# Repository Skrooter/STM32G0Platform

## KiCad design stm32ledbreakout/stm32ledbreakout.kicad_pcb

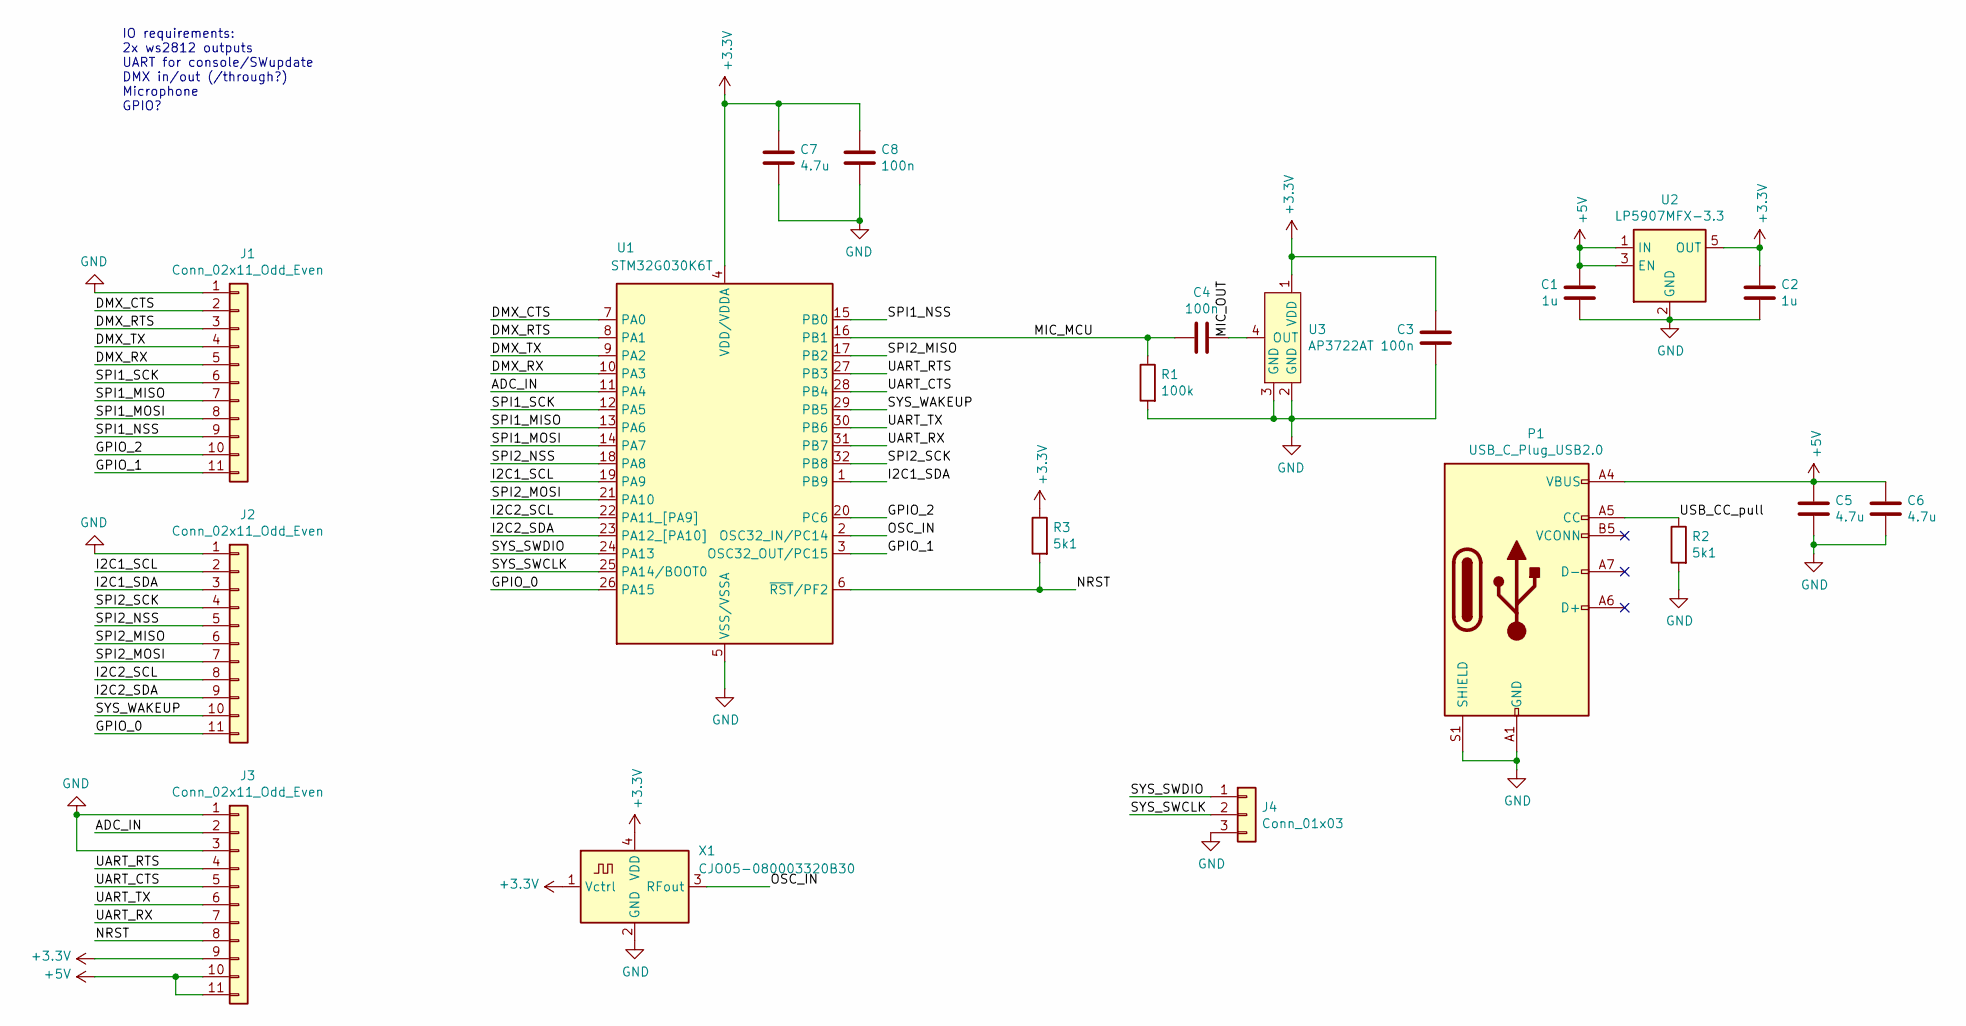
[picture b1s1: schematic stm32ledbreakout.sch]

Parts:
C1, C2: 1u; C_0603_1608Metric_Pad1.08x0.95mm_HandSolder
C3, C4, C8: 100n; C_0603_1608Metric_Pad1.08x0.95mm_HandSolder
C5, C6, C7: 4.7u; C_0603_1608Metric_Pad1.08x0.95mm_HandSolder
J1, J2, J3: Conn_02x11_Odd_Even; Castillation_11_P2.54mm
J4: Conn_01x03; PinSocket_1x03_P2.54mm_Vertical
P1: USB_C_Plug_USB2.0; USB_C_Receptacle_HRO_TYPE-C-31-M-12
R1: 100k; R_0603_1608Metric
R2, R3: 5k1; R_0603_1608Metric
U1: STM32G030K6T; LQFP-32_7x7mm_P0.8mm
U2: LP5907MFX-3.3; SOT-23-5
U3: AP3722AT
X1: CJO05-080003320B30; Oscillator_SMD_Abracon_ASE-4Pin_3.2x2.5mm_HandSoldering

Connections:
+3V3: C2.1, C3.1, C7.1, C8.2, J3.9, R3.1, U1.4 (VDD/VDDA), U2.5 (OUT), U3.1 (VDD), X1.1 (Vctrl), X1.4 (VDD)
+5V: C1.2, C5.1, C6.1, J3.10, J3.11, P1.A4 (VBUS), P1.A9 (VBUS), P1.B4 (VBUS), P1.B9 (VBUS), U2.1 (IN), U2.3 (EN)
/ADC_IN: J3.2, U1.11 (PA4)
/DMX_CTS: J1.2, U1.7 (PA0)
/DMX_RTS: J1.3, U1.8 (PA1)
/DMX_RX: J1.5, U1.10 (PA3)
/DMX_TX: J1.4, U1.9 (PA2)
/GPIO_0: J2.11, U1.26 (PA15)
/GPIO_1: J1.11, U1.3 (OSC32_OUT/PC15)
/GPIO_2: J1.10, U1.20 (PC6)
/I2C1_SCL: J2.2, U1.19 (PA9)
/I2C1_SDA: J2.3, U1.1 (PB9)
/I2C2_SCL: J2.8, U1.22 (PA11_[PA9])
/I2C2_SDA: J2.9, U1.23 (PA12_[PA10])
/MIC_MCU: C4.1, R1.1, U1.16 (PB1)
/MIC_OUT: C4.2, U3.4 (OUT)
/NRST: J3.8, R3.2, U1.6 (~RST~/PF2)
/OSC_IN: U1.2 (OSC32_IN/PC14), X1.3 (RFout)
/SPI1_MISO: J1.7, U1.13 (PA6)
/SPI1_MOSI: J1.8, U1.14 (PA7)
/SPI1_NSS: J1.9, U1.15 (PB0)
/SPI1_SCK: J1.6, U1.12 (PA5)
/SPI2_MISO: J2.6, U1.17 (PB2)
/SPI2_MOSI: J2.7, U1.21 (PA10)
/SPI2_NSS: J2.5, U1.18 (PA8)
/SPI2_SCK: J2.4, U1.32 (PB8)
/SYS_SWCLK: J4.2, U1.25 (PA14/BOOT0)
/SYS_SWDIO: J4.1, U1.24 (PA13)
/SYS_WAKEUP: J2.10, U1.29 (PB5)
/UART_CTS: J3.5, U1.28 (PB4)
/UART_RTS: J3.4, U1.27 (PB3)
/UART_RX: J3.7, U1.31 (PB7)
/UART_TX: J3.6, U1.30 (PB6)
/USB_CC_pull: P1.A5 (CC), R2.1
GND: C1.1, C2.2, C3.2, C5.2, C6.2, C7.2, C8.1, J1.1, J2.1, J3.1, J3.3, J4.3, P1.A1 (GND), P1.A12 (GND), P1.B1 (GND), P1.B12 (GND), P1.S1 (SHIELD), R1.2, R2.2, U1.5 (VSS/VSSA), U2.2 (GND), U3.2 (GND), U3.3 (GND), X1.2 (GND)

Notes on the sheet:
IO requirements: 2x ws2812 outputs UART for console/SWupdate DMX in/out (/through?) Microphone GPIO?

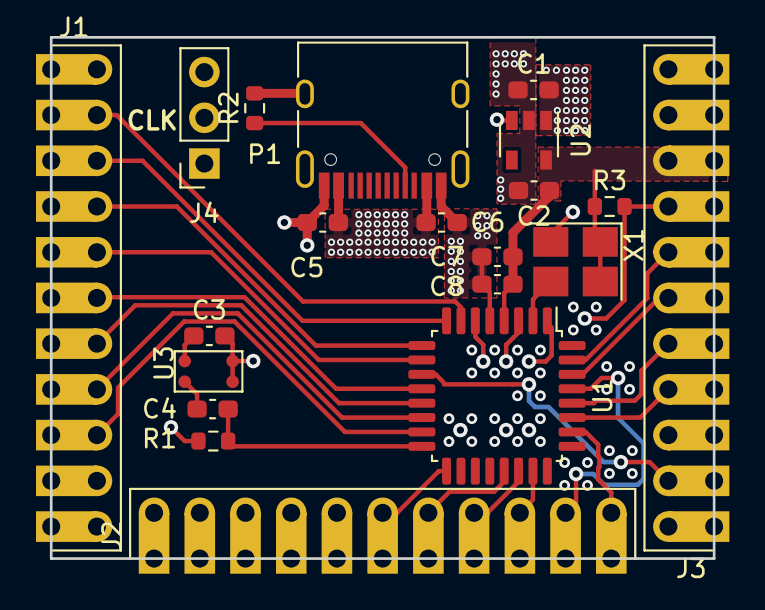
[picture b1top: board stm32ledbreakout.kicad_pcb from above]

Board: 4 copper layers, 36.8 x 29.0 mm, 20 parts (0 on the bottom side), 35 nets.

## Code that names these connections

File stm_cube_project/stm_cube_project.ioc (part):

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PA6.Mode=Full_Duplex_Master
PA11\ [PA9].Mode=I2C
Mcu.UserName=STM32G030K6Tx
PA12\ [PA10].Mode=I2C
PA0.GPIO_Label=DMX_CTS
PA14-BOOT0.Mode=Serial_Wire
PC6.GPIO_Label=GPIO_2
PA3.GPIOParameters=GPIO_Label
PB6.GPIO_Label=UART_TX
PA2.GPIOParameters=GPIO_Label
RCC.SYSCLKSource=RCC_SYSCLKSOURCE_PLLCLK
PC14-OSC32_IN\ (PC14).Mode=HSE-External-Clock-Source
PB4.GPIOParameters=GPIO_Label
PC15-OSC32_OUT\ (PC15).GPIOParameters=GPIO_Label
PA4.Mode=IN4
PA12\ [PA10].Signal=I2C2_SDA
PB6.Signal=USART1_TX
PB6.Mode=Asynchronous
PA14-BOOT0.Signal=SYS_SWCLK
RCC.HSE_VALUE=8000000
PB2.Signal=SPI2_MISO
PB3.Mode=CTS_RTS
PA1.GPIOParameters=GPIO_Label
PB4.Mode=CTS_RTS
PB1.GPIO_Label=MIC_IN
PB5.Mode=SYS_WakeUp6
PA0.Mode=CTS_RTS
PB3.GPIOParameters=GPIO_Label
PB7.Signal=USART1_RX
PA8.Signal=SPI2_NSS
PB6.GPIOParameters=GPIO_Label
PA0.Signal=USART2_CTS
PB7.GPIO_Label=UART_RX
Mcu.Package=LQFP32
PB9.Signal=I2C1_SDA
PB1.Signal=ADC1_IN9
PA6.Signal=SPI1_MISO
PA2.GPIO_Label=DMX_TX
PA10.Signal=SPI2_MOSI
PA15.Signal=GPIO_Output
PA4.GPIO_Label=ADC_IN
PB4.Signal=USART1_CTS
PA3.Signal=USART2_RX
PA5.Mode=Full_Duplex_Master
PB3.GPIO_Label=UART_RTS
PC15-OSC32_OUT\ (PC15).GPIO_Label=GPIO_1
PA7.Mode=Full_Duplex_Master
PA10.Mode=Full_Duplex_Master
PC6.Signal=GPIO_Output
PC15-OSC32_OUT\ (PC15).Signal=GPIO_Input
PA13.Signal=SYS_SWDIO
PA3.Mode=Asynchronous
PA9.Mode=I2C
PB7.GPIOParameters=GPIO_Label
PB9.Mode=I2C
PA9.Signal=I2C1_SCL
PA1.Signal=USART2_RTS
PA5.Signal=SPI1_SCK
PB0.Mode=NSS_Signal_Hard_Output
board=custom
PA1.Mode=CTS_RTS
PB4.GPIO_Label=UART_CTS
PA1.GPIO_Label=DMX_RTS
PA4.GPIOParameters=GPIO_Label
PA13.Mode=Serial_Wire
Mcu.Name=STM32G030K(6-8)Tx
PA11\ [PA9].Signal=I2C2_SCL
PA2.Signal=USART2_TX
PB3.Signal=USART1_RTS
PA4.Signal=ADC1_IN4
RCC.SYSCLKFreq_VALUE=64000000
PB5.Signal=SYS_WKUP6
PC14-OSC32_IN\ (PC14).Signal=RCC_OSC_IN
PB2.Mode=Full_Duplex_Master
PB7.Mode=Asynchronous
PA0.GPIOParameters=GPIO_Label
PB1.Mode=IN9
PC6.GPIOParameters=GPIO_Label
PB8.Mode=Full_Duplex_Master
PA2.Mode=Asynchronous
PB8.Signal=SPI2_SCK
PA8.Mode=NSS_Signal_Hard_Output
PB0.Signal=SPI1_NSS
PA3.GPIO_Label=DMX_RX
PB1.GPIOParameters=GPIO_Label
PA7.Signal=SPI1_MOSI
